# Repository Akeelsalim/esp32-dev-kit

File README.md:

# 🛠️ ESP32 DevKit Clone – KiCad Project

This project is a custom PCB design of the **ESP32 DevKit**, created using  latest version of **KiCad 9.0.3**. The design is based on the official **ESP32-DevKitC-v4** reference schematic from Espressif, with modifications to suit custom layout preferences and component placement.Gerber files are attached.

---

### 📷 Project Images
# Schematic

# PCB Layout

# ERC

# DRC

# 3D top view

# 3D bottom view

# BOM

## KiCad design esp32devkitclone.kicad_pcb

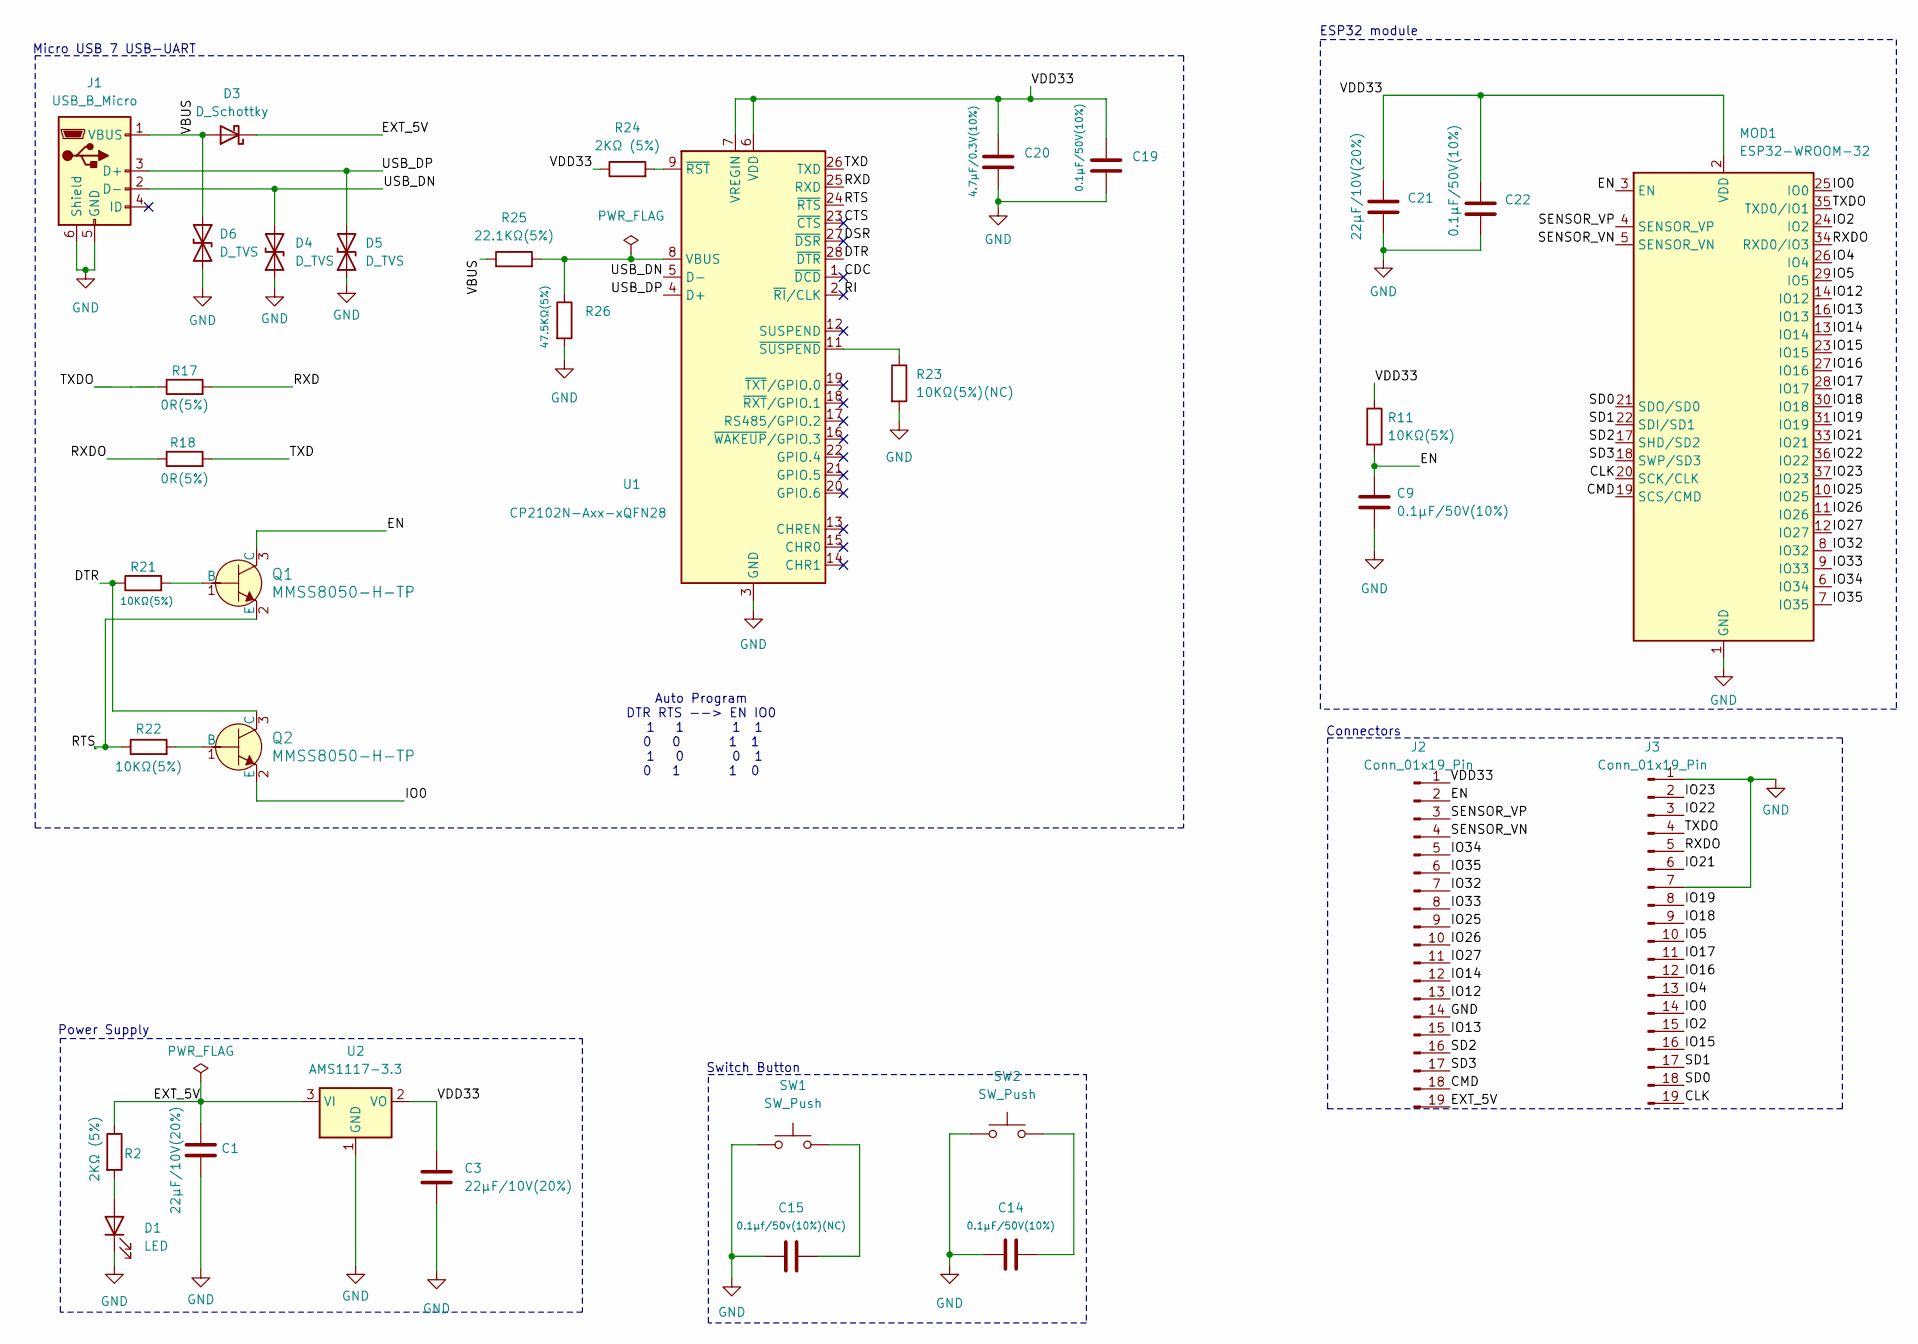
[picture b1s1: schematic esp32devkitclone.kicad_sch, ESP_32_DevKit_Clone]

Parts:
C1, C3, C21: 22µF/10V(20%); C_0201_0603Metric
C9, C14, C19, C22: 0.1µF/50V(10%); C_01005_0402Metric
C15: 0.1µf/50v(10%)(NC); C_01005_0402Metric
C20: 4.7µF/0.3V(10%); C_01005_0402Metric
D1: LED; LED_0603_1608Metric
D3: D_Schottky; D_SOD-323
D4, D5, D6: D_TVS; D_SOD-523
J1: USB_B_Micro; USB_Micro-AB_Molex_47590-0001
J2, J3: Conn_01x19_Pin; PinSocket_1x19_P2.54mm_Vertical
MOD1: ESP32-WROOM-32; ESP32-WROOM-32D
Q1, Q2: MMSS8050-H-TP; SOT-23-3; MPN MMSS8050-H-TP; Digi-Key_PN MMSS8050-H-TPMSCT-ND
R2, R24: 2KΩ (5%); R_01005_0402Metric
R11, R21, R22: 10KΩ(5%); R_01005_0402Metric
R17, R18: 0R(5%); R_01005_0402Metric
R23: 10KΩ(5%)(NC); R_01005_0402Metric
R25: 22.1KΩ(5%); R_01005_0402Metric
R26: 47.5KΩ(5%); R_01005_0402Metric
SW1, SW2: SW_Push; SW_SPST_B3S-1000
U1: CP2102N-Axx-xQFN28; TQFN-28-1EP_5x5mm_P0.5mm_EP2.7x2.7mm
U2: AMS1117-3.3; SOT-223-3_TabPin2

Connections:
/CDC: U1.1 (~DCD)
/CLK: J3.19, MOD1.20 (SCK/CLK)
/CMD: J2.18, MOD1.19 (SCS/CMD)
/CTS: U1.23 (~CTS)
/DSR: U1.27 (~DSR)
/DTR: Q2.3 (C), R21.1, U1.28 (~DTR)
/EN: C9.1, J2.2, MOD1.3 (EN), Q1.3 (C), R11.2
/EXT_5V: C1.1, D3.1 (K), J2.19, R2.1, U2.3 (VI)
/IO0: J3.14, MOD1.25 (IO0), Q2.2 (E)
/IO2: J3.15, MOD1.24 (IO2)
/IO4: J3.13, MOD1.26 (IO4)
/IO5: J3.10, MOD1.29 (IO5)
/IO12: J2.13, MOD1.14 (IO12)
/IO13: J2.15, MOD1.16 (IO13)
/IO14: J2.12, MOD1.13 (IO14)
/IO15: J3.16, MOD1.23 (IO15)
/IO16: J3.12, MOD1.27 (IO16)
/IO17: J3.11, MOD1.28 (IO17)
/IO18: J3.9, MOD1.30 (IO18)
/IO19: J3.8, MOD1.31 (IO19)
/IO21: J3.6, MOD1.33 (IO21)
/IO22: J3.3, MOD1.36 (IO22)
/IO23: J3.2, MOD1.37 (IO23)
/IO25: J2.9, MOD1.10 (IO25)
/IO26: J2.10, MOD1.11 (IO26)
/IO27: J2.11, MOD1.12 (IO27)
/IO32: J2.7, MOD1.8 (IO32)
/IO33: J2.8, MOD1.9 (IO33)
/IO34: J2.5, MOD1.6 (IO34)
/IO35: J2.6, MOD1.7 (IO35)
/RI: U1.2 (~RI/CLK)
/RTS: Q1.2 (E), R22.1, U1.24 (~RTS)
/RXD: R17.2, U1.25 (RXD)
/RXDO: J3.5, MOD1.34 (RXD0/IO3), R18.1
/SD0: J3.18, MOD1.21 (SDO/SD0)
/SD1: J3.17, MOD1.22 (SDI/SD1)
/SD2: J2.16, MOD1.17 (SHD/SD2)
/SD3: J2.17, MOD1.18 (SWP/SD3)
/SENSOR_VN: J2.4, MOD1.5 (SENSOR_VN)
/SENSOR_VP: J2.3, MOD1.4 (SENSOR_VP)
/TXD: R18.2, U1.26 (TXD)
/TXDO: J3.4, MOD1.35 (TXD0/IO1), R17.1
/USB_DN: D4.2 (A2), J1.2 (D-), U1.5 (D-)
/USB_DP: D5.2 (A2), J1.3 (D+), U1.4 (D+)
/VBUS: D3.2 (A), D6.1 (A1), J1.1 (VBUS), R25.1
/VDD33: C3.1, C19.1, C20.1, C21.1, C22.1, J2.1, MOD1.2 (VDD), R11.1, R24.1, U1.6 (VDD), U1.7 (VREGIN), U2.2 (VO)
GND: C1.2, C3.2, C9.2, C14.1, C15.1, C19.2, C20.2, C21.2, C22.2, D1.1 (K), D4.1 (A1), D5.1 (A1), D6.2 (A2), J1.5 (GND), J1.6 (Shield), J2.14, J3.1, J3.7, MOD1.1 (GND), MOD1.15 (GND), MOD1.38 (GND), MOD1.39 (GND), R23.2, R26.2, SW1.1, SW2.1, U1.3 (GND), U1.29 (GND), U2.1 (GND)
unnamed: C14.2, SW2.2
unnamed: C15.2, SW1.2
unnamed: D1.2 (A), R2.2
unnamed: Q1.1 (B), R21.2
unnamed: Q2.1 (B), R22.2
unnamed: R25.2, R26.1, U1.8 (VBUS)
unnamed: R24.2, U1.9 (~RST)
unnamed: R23.1, U1.11 (~SUSPEND)

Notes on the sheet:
Connectors
ESP32 module
Power Supply
Auto Program DTR RTS --> EN IO0 1 1 1 1 0 0 1 1 1 0 0 1 0 1 1 0
Switch Button
Micro USB 7 USB-UART

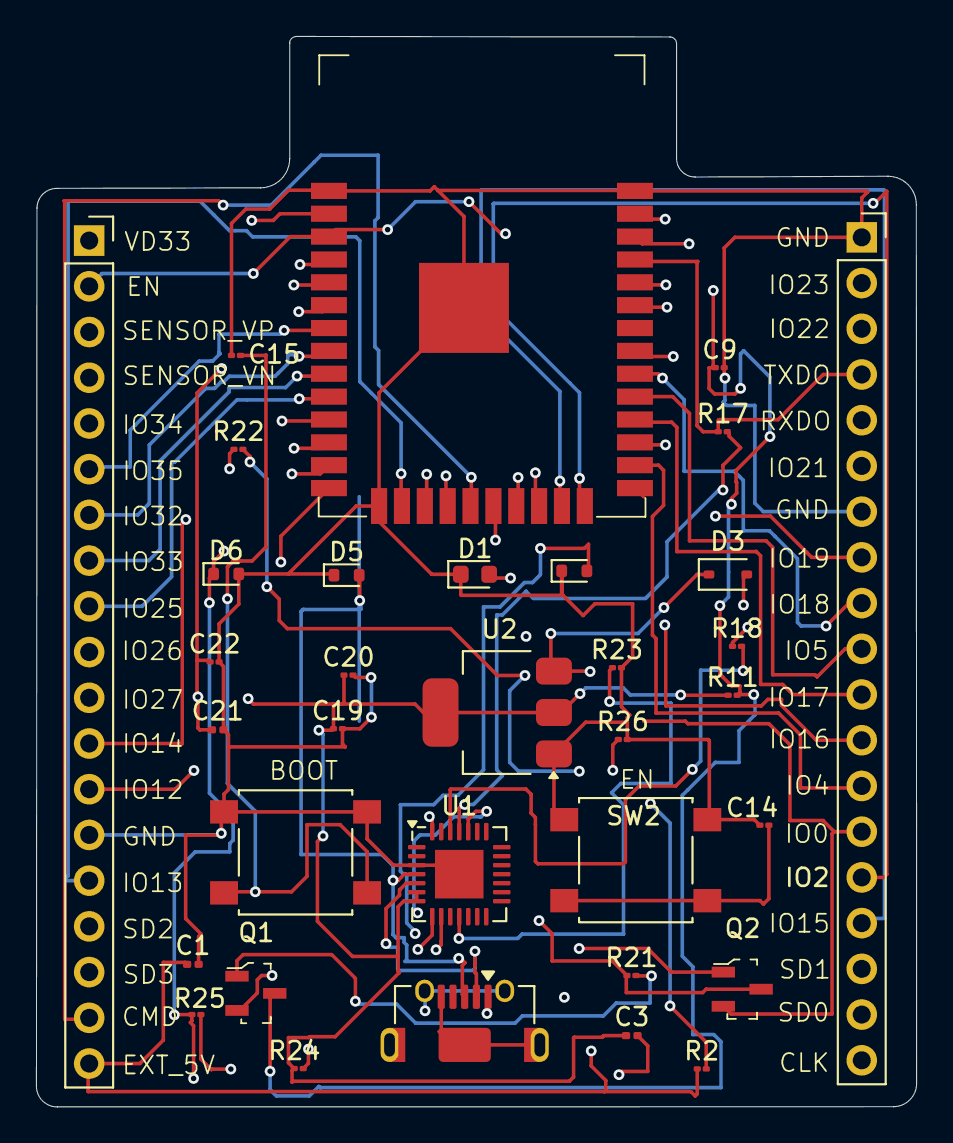
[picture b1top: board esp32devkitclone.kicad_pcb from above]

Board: 4 copper layers, 48.9 x 59.5 mm, 34 parts (0 on the bottom side), 51 nets.

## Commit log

2025-07-09 Create images
2025-07-09 Create sd
2025-07-09 readme with necessary images
